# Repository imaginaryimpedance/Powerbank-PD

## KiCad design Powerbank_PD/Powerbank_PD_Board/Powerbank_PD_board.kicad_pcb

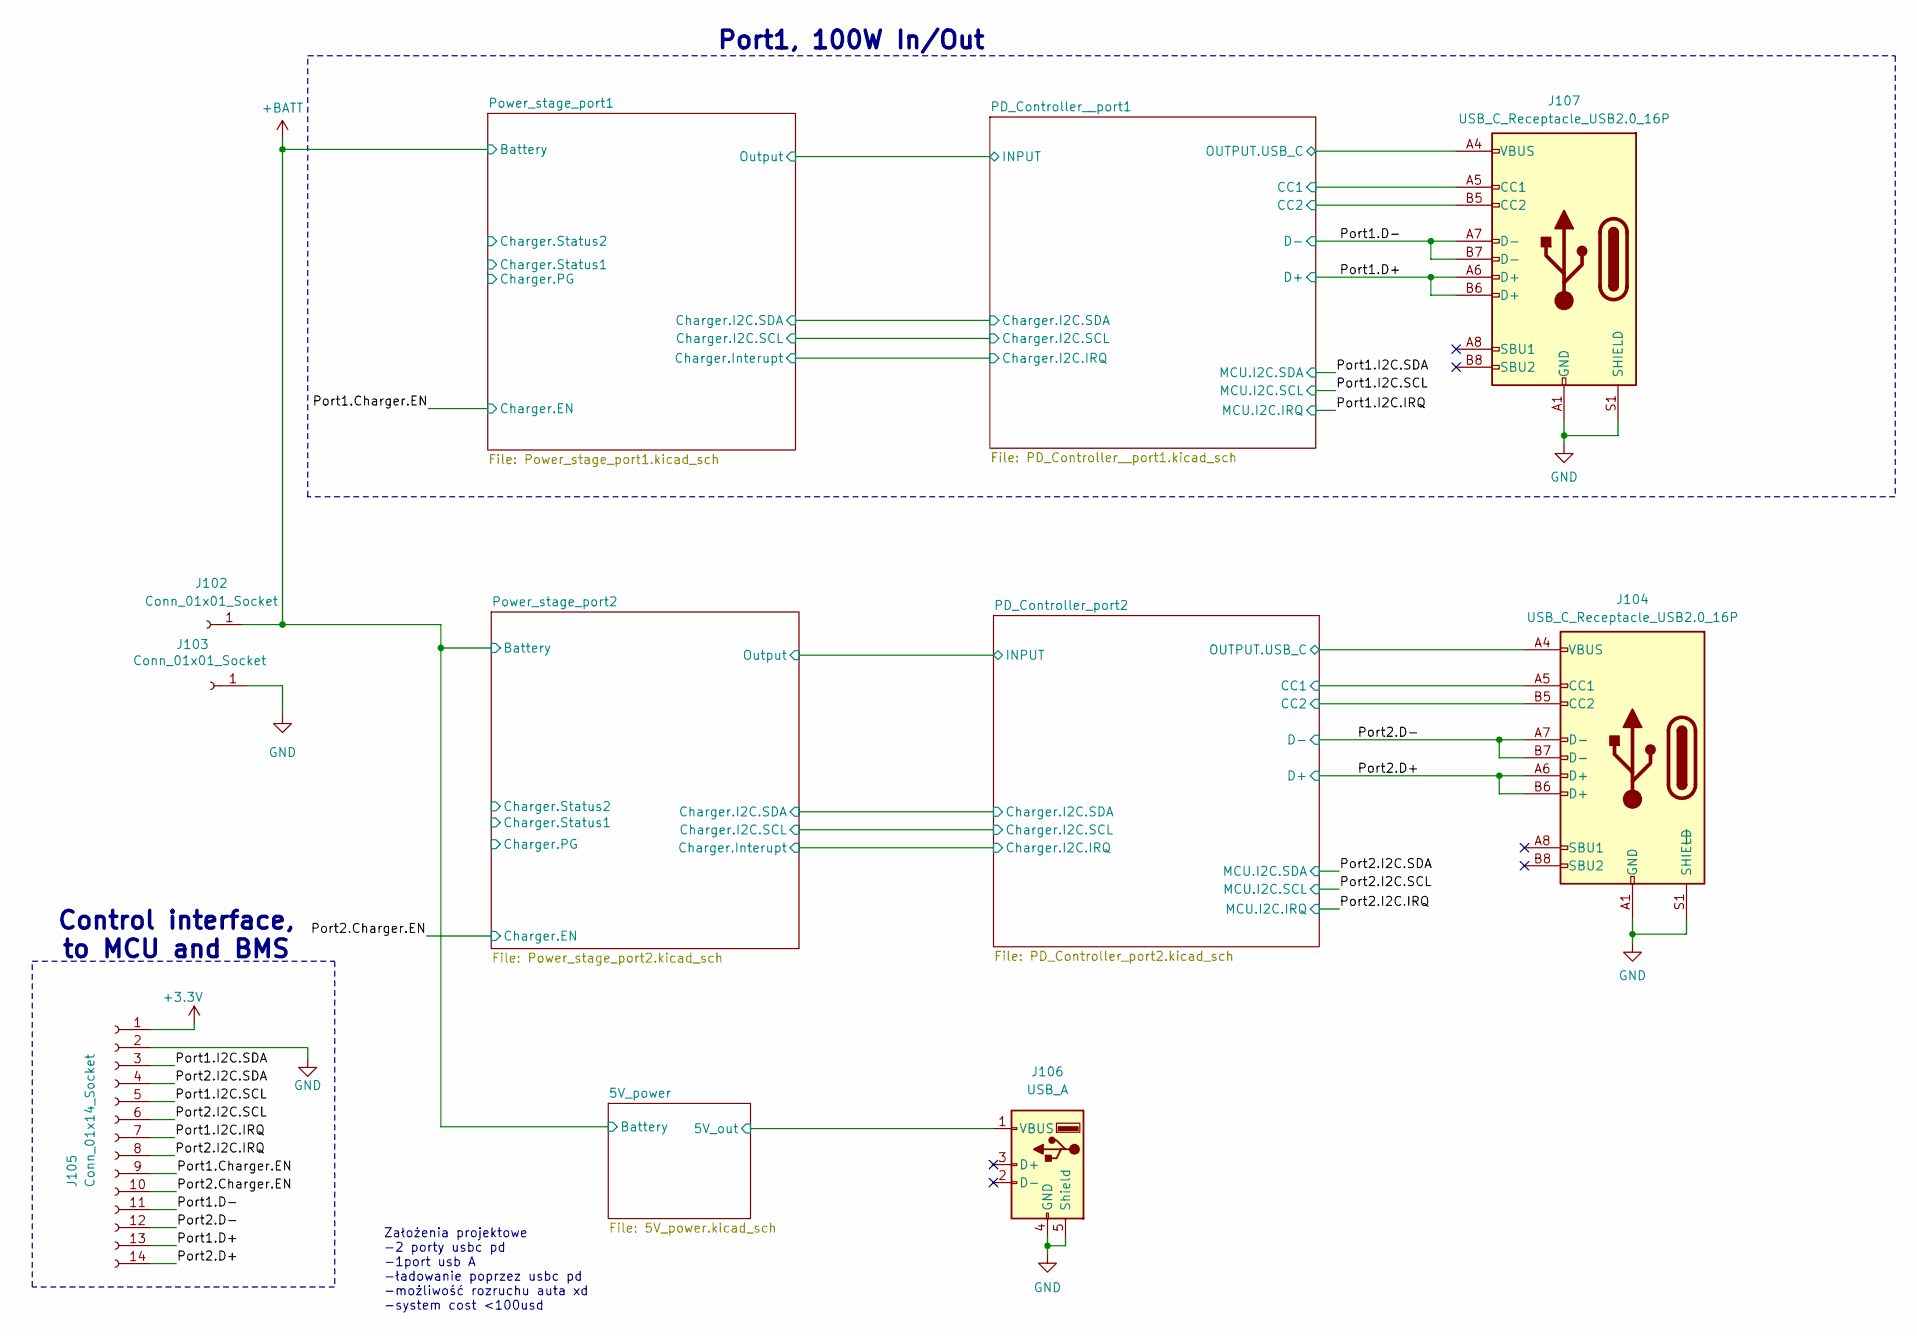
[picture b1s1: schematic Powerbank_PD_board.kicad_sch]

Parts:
J102, J103: Conn_01x01_Socket; TestPoint_Pad_4.0x4.0mm
J104, J107: USB_C_Receptacle_USB2.0_16P; USB_C_Receptacle_GCT_USB4110
J105: Conn_01x14_Socket; PinHeader_2x07_P1.00mm_Vertical_SMD
J106: USB_A; USB_A_CNCTech_1001-011-01101_Horizontal

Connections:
+3.3V: J105.1; also elsewhere on the board
+5V: J106.1 (VBUS); also elsewhere on the board
+BATT: J102.1; also elsewhere on the board
/PD_Controller__port1/CC1: J107.A5 (CC1); also elsewhere on the board
/PD_Controller__port1/CC2: J107.B5 (CC2); also elsewhere on the board
/PD_Controller__port1/OUTPUT.USB_C: J107.A4 (VBUS), J107.A9 (VBUS), J107.B4 (VBUS), J107.B9 (VBUS); also elsewhere on the board
/PD_Controller_port2/CC1: J104.A5 (CC1); also elsewhere on the board
/PD_Controller_port2/CC2: J104.B5 (CC2); also elsewhere on the board
/PD_Controller_port2/OUTPUT.USB_C: J104.A4 (VBUS), J104.A9 (VBUS), J104.B4 (VBUS), J104.B9 (VBUS); also elsewhere on the board
/Port1.Charger.EN: J105.9; also elsewhere on the board
/Port1.D+: J105.13, J107.A6 (D+), J107.B6 (D+); also elsewhere on the board
/Port1.D-: J105.11, J107.A7 (D-), J107.B7 (D-); also elsewhere on the board
/Port1.I2C.IRQ: J105.7; also elsewhere on the board
/Port1.I2C.SCL: J105.5; also elsewhere on the board
/Port1.I2C.SDA: J105.3; also elsewhere on the board
/Port2.Charger.EN: J105.10; also elsewhere on the board
/Port2.D+: J104.A6 (D+), J104.B6 (D+), J105.14; also elsewhere on the board
/Port2.D-: J104.A7 (D-), J104.B7 (D-), J105.12; also elsewhere on the board
/Port2.I2C.IRQ: J105.8; also elsewhere on the board
/Port2.I2C.SCL: J105.6; also elsewhere on the board
/Port2.I2C.SDA: J105.4; also elsewhere on the board
GND: J103.1, J104.A1 (GND), J104.A12 (GND), J104.B1 (GND), J104.B12 (GND), J104.S1 (SHIELD), J105.2, J106.4 (GND), J106.5 (Shield), J107.A1 (GND), J107.A12 (GND), J107.B1 (GND), J107.B12 (GND), J107.S1 (SHIELD); also elsewhere on the board

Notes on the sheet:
Control interface, to MCU and BMS
Założenia projektowe -2 porty usbc pd -1port usb A -ładowanie poprzez usbc pd -możliwość rozruchu auta xd -system cost <100usd
Port1, 100W In/Out

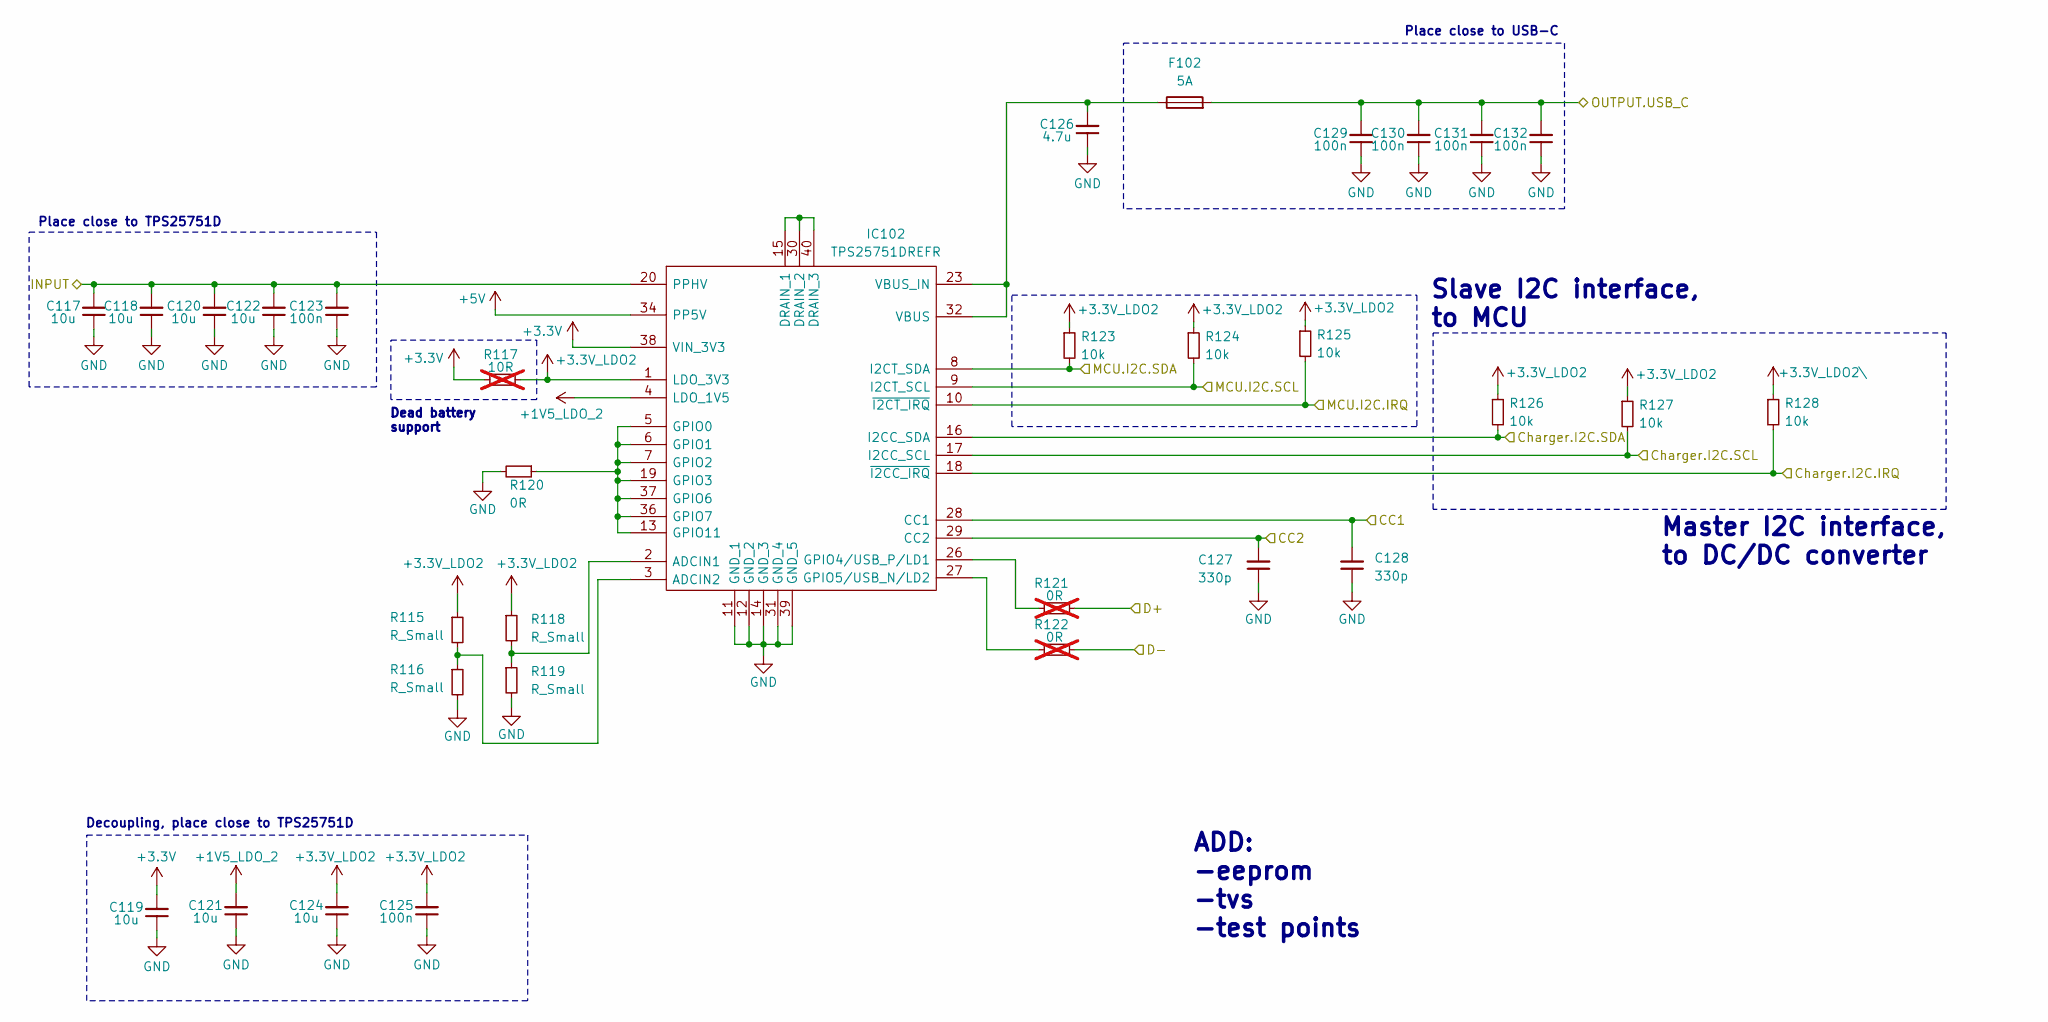
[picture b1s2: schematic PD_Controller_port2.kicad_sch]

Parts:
C117, C118, C119, C120, C121, C122, C124: 10u; C_0603_1608Metric
C123, C125, C129, C130, C131, C132: 100n; C_0603_1608Metric
C126: 4.7u; C_0603_1608Metric
C127, C128: 330p; C_0603_1608Metric
F102: 5A; Fuse_1206_3216Metric
IC102: TPS25751DREFR; Manufacturer_Part_Number TPS25751DREFR; Mouser Part Number 595-TPS25751DREFR
R115, R116, R118, R119: R_Small; R_0603_1608Metric
R117: 10R; R_0603_1608Metric; not fitted
R120: 0R; R_0603_1608Metric
R121, R122: 0R; R_0603_1608Metric; not fitted
R123, R124, R125, R126, R127, R128: 10k; R_0603_1608Metric

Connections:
+1V5_LDO_2: C121.2, IC102.4 (LDO_1V5)
+3.3V: C119.2, IC102.38 (VIN_3V3), R117.1; also elsewhere on the board
+3.3V_LDO2: C124.2, C125.2, IC102.1 (LDO_3V3), R115.1, R117.2, R118.1, R123.1, R124.1, R125.1, R126.1, R127.1
+3.3V_LDO2\: R128.1
+5V: IC102.34 (PP5V); also elsewhere on the board
/PD_Controller_port2/CC1: C128.2, IC102.28 (CC1); also elsewhere on the board
/PD_Controller_port2/CC2: C127.2, IC102.29 (CC2); also elsewhere on the board
/PD_Controller_port2/Charger.I2C.IRQ: IC102.18 (~I2CC_IRQ), R128.2; also elsewhere on the board
/PD_Controller_port2/Charger.I2C.SCL: IC102.17 (I2CC_SCL), R127.2; also elsewhere on the board
/PD_Controller_port2/Charger.I2C.SDA: IC102.16 (I2CC_SDA), R126.2; also elsewhere on the board
/PD_Controller_port2/INPUT: C117.2, C118.2, C120.2, C122.2, C123.2, IC102.20 (PPHV); also elsewhere on the board
/PD_Controller_port2/OUTPUT.USB_C: C129.2, C130.2, C131.2, C132.2, F102.2; also elsewhere on the board
/Port2.D+: R121.2; also elsewhere on the board
/Port2.D-: R122.2; also elsewhere on the board
/Port2.I2C.IRQ: IC102.10 (~I2CT_IRQ), R125.2; also elsewhere on the board
/Port2.I2C.SCL: IC102.9 (I2CT_SCL), R124.2; also elsewhere on the board
/Port2.I2C.SDA: IC102.8 (I2CT_SDA), R123.2; also elsewhere on the board
GND: C117.1, C118.1, C119.1, C120.1, C121.1, C122.1, C123.1, C124.1, C125.1, C126.1, C127.1, C128.1, C129.1, C130.1, C131.1, C132.1, IC102.11 (GND_1), IC102.12 (GND_2), IC102.14 (GND_3), IC102.31 (GND_4), IC102.39 (GND_5), R116.2, R119.2, R120.2; also elsewhere on the board
unnamed: IC102.2 (ADCIN1), R118.2, R119.1
unnamed: IC102.3 (ADCIN2), R115.2, R116.1
unnamed: IC102.15 (DRAIN_1), IC102.30 (DRAIN_2), IC102.40 (DRAIN_3)
unnamed: IC102.5 (GPIO0), IC102.6 (GPIO1), IC102.7 (GPIO2), IC102.13 (GPIO11), IC102.19 (GPIO3), IC102.36 (GPIO7), IC102.37 (GPIO6), R120.1
unnamed: IC102.26 (GPIO4/USB_P/LD1), R121.1
unnamed: IC102.27 (GPIO5/USB_N/LD2), R122.1
unnamed: C126.2, F102.1, IC102.23 (VBUS_IN), IC102.32 (VBUS)

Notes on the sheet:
Slave I2C interface, to MCU
Master I2C interface, to DC/DC converter
ADD: -eeprom -tvs -test points
Place close to USB-C
Dead battery support
Decoupling, place close to TPS25751D
Place close to TPS25751D

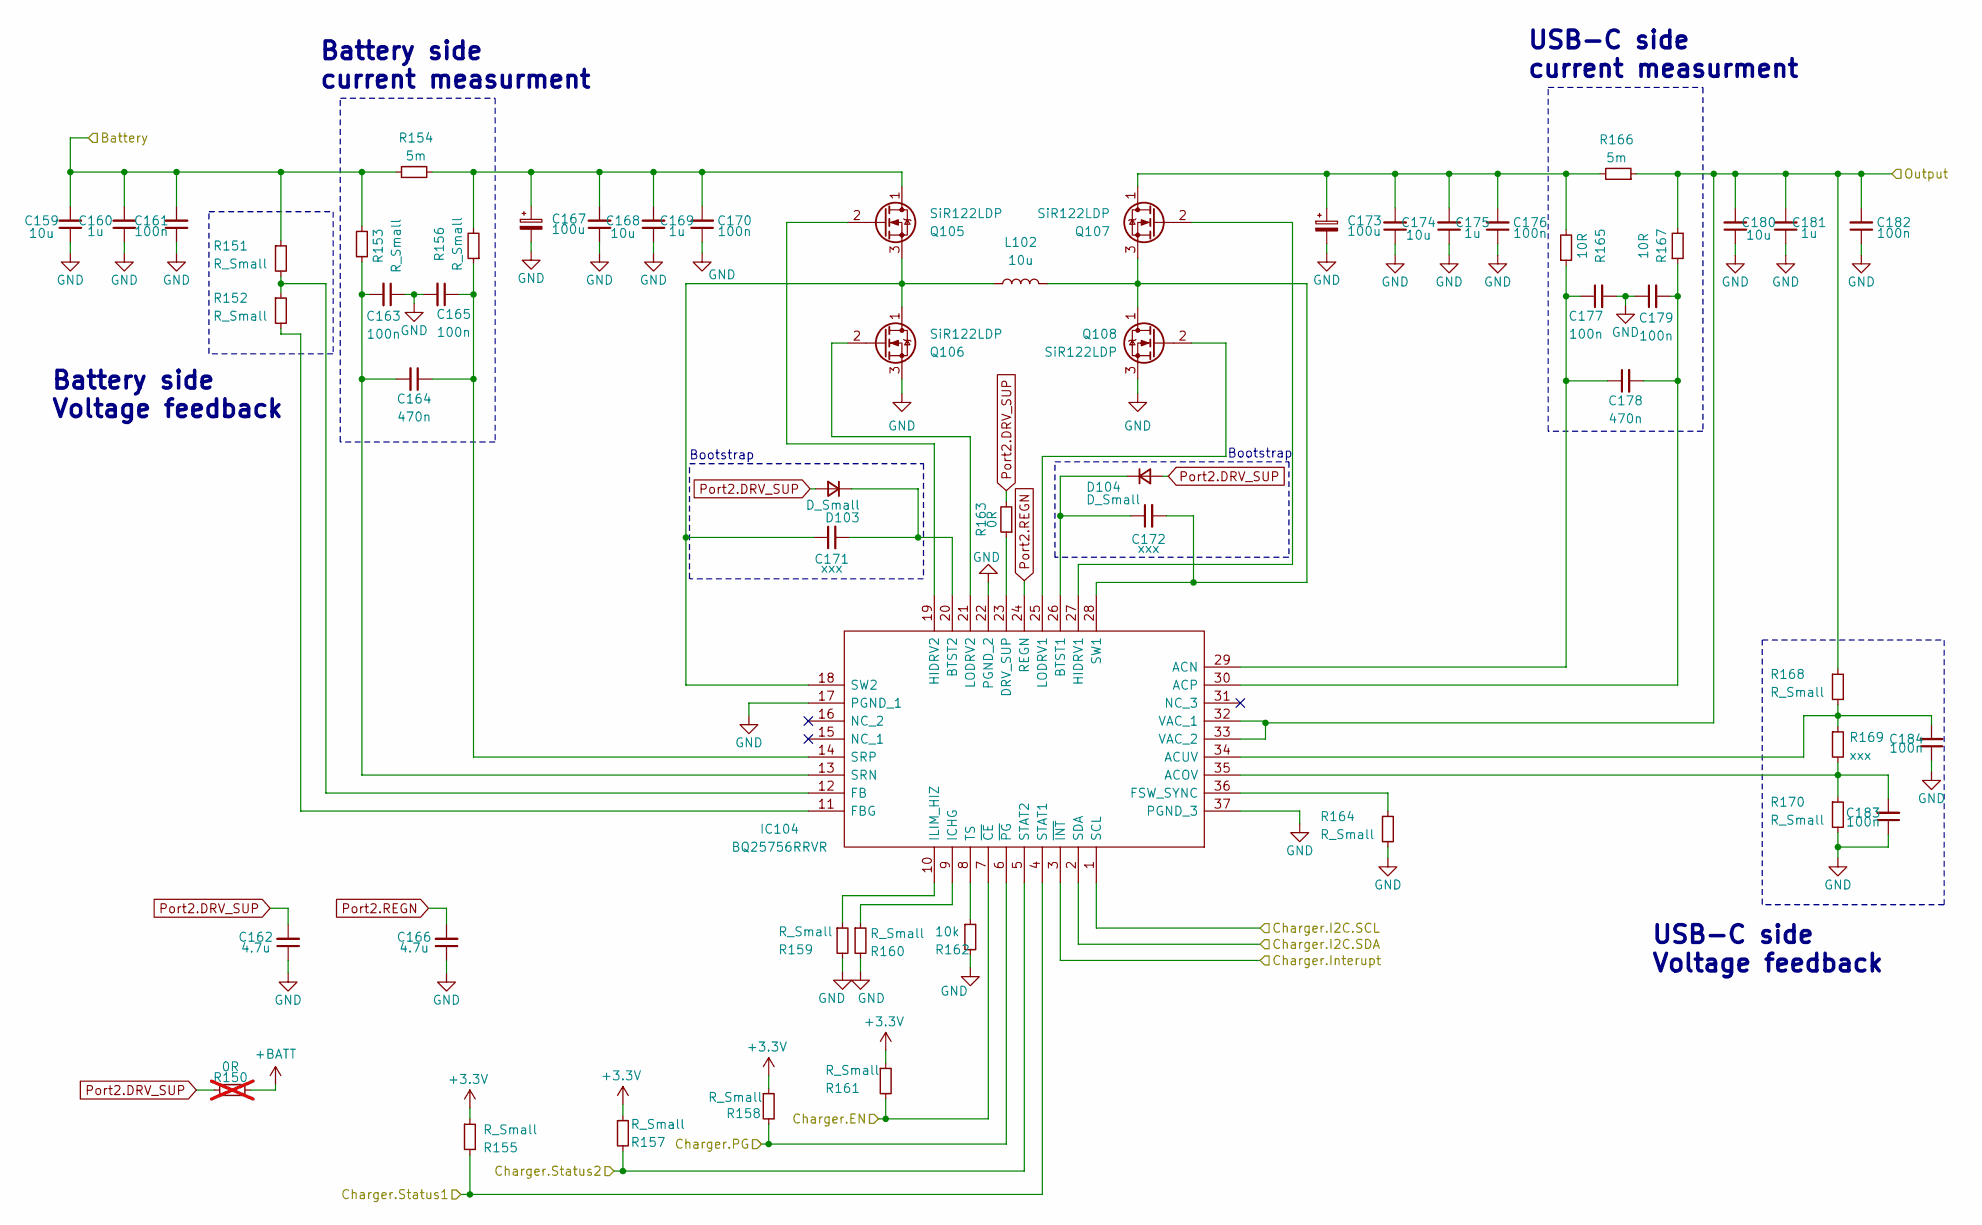
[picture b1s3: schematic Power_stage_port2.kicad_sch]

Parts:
C159, C168, C174: 10u; C_0603_1608Metric
C160, C169, C175: 1u; C_0603_1608Metric
C161, C163, C165, C170, C176, C177, C179, C183, C184: 100n; C_0603_1608Metric
C162, C166: 4.7u; C_0603_1608Metric
C164, C178: 470n; C_0603_1608Metric
C167, C173: 100u; CP_Elec_6.3x7.7
C171, C172: xxx; C_0603_1608Metric
C180: 10u; C_0805_2012Metric
C181: 1u; C_0805_2012Metric
C182: 100n; C_0805_2012Metric
D103, D104: D_Small; D_SOD-123
IC104: BQ25756RRVR; QFN50P500X600X100-37N-D; Manufacturer_Part_Number BQ25756RRVR; Mouser Part Number 595-BQ25756RRVR
L102: 10u; L_Coilcraft_XxL4040
Q105, Q106, Q107, Q108: SiR122LDP; PowerPAK_SO-8_Single
R150: 0R; R_0603_1608Metric; not fitted
R151, R152, R153, R155, R156, R157, R158, R159, R160, R161, R164, R168, R170: R_Small; R_0603_1608Metric
R154, R166: 5m; R_2512_6332Metric
R162: 10k; R_0603_1608Metric
R163: 0R; R_0603_1608Metric
R165, R167: 10R; R_0603_1608Metric
R169: xxx; R_0603_1608Metric

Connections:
+3.3V: R155.1, R157.1, R158.1, R161.1; also elsewhere on the board
+BATT: C159.2, C160.2, C161.2, R150.1, R151.1, R153.2, R154.1; also elsewhere on the board
/PD_Controller_port2/Charger.I2C.IRQ: IC104.3 (~INT); also elsewhere on the board
/PD_Controller_port2/Charger.I2C.SCL: IC104.1 (SCL); also elsewhere on the board
/PD_Controller_port2/Charger.I2C.SDA: IC104.2 (SDA); also elsewhere on the board
/PD_Controller_port2/INPUT: C180.2, C181.2, C182.2, IC104.32 (VAC_1), IC104.33 (VAC_2), R166.1, R167.2, R168.1; also elsewhere on the board
/Port2.Charger.EN: IC104.7 (~CE), R161.2; also elsewhere on the board
/Power_stage_port2/Charger.PG: IC104.6 (~PG), R158.2
/Power_stage_port2/Charger.Status1: IC104.4 (STAT1), R155.2
/Power_stage_port2/Charger.Status2: IC104.5 (STAT2), R157.2
GND: C159.1, C160.1, C161.1, C162.1, C163.1, C165.2, C166.1, C167.2, C168.1, C169.1, C170.1, C173.2, C174.1, C175.1, C176.1, C177.2, C179.1, C180.1, C181.1, C182.1, C183.1, C184.1, IC104.17 (PGND_1), IC104.22 (PGND_2), IC104.37 (PGND_3), Q106.3 (S), Q108.3 (S), R159.2, R160.2, R162.2, R164.2, R170.2; also elsewhere on the board
unnamed: C171.2, D103.1 (K), IC104.20 (BTST2)
unnamed: C172.1, D104.1 (K), IC104.26 (BTST1)
unnamed: C177.1, C178.1, IC104.29 (ACN), R165.1
unnamed: C183.2, IC104.35 (ACOV), R169.2, R170.1
unnamed: C178.2, C179.2, IC104.30 (ACP), R167.1
unnamed: C184.2, IC104.34 (ACUV), R168.2, R169.1
unnamed: IC104.23 (DRV_SUP), R163.1
unnamed: IC104.12 (FB), R151.2, R152.1
unnamed: IC104.11 (FBG), R152.2
unnamed: IC104.36 (FSW_SYNC), R164.1
unnamed: IC104.27 (HIDRV1), Q107.2 (G)
unnamed: IC104.19 (HIDRV2), Q105.2 (G)
unnamed: IC104.9 (ICHG), R160.1
unnamed: IC104.10 (ILIM_HIZ), R159.1
unnamed: IC104.25 (LODRV1), Q108.2 (G)
unnamed: IC104.21 (LODRV2), Q106.2 (G)
unnamed: C163.2, C164.2, IC104.13 (SRN), R153.1
unnamed: C164.1, C165.1, IC104.14 (SRP), R156.1
unnamed: C172.2, IC104.28 (SW1), L102.2, Q107.3 (S), Q108.1 (D)
unnamed: C171.1, IC104.18 (SW2), L102.1, Q105.3 (S), Q106.1 (D)
unnamed: IC104.8 (TS), R162.1
unnamed: C167.1, C168.2, C169.2, C170.2, Q105.1 (D), R154.2, R156.2
unnamed: C173.1, C174.2, C175.2, C176.2, Q107.1 (D), R165.2, R166.2
Port2.DRV_SUP: C162.2, D103.2 (A), D104.2 (A), R150.2, R163.2
Port2.REGN: C166.2, IC104.24 (REGN)

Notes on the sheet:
Bootstrap
USB-C side current measurment
Battery side current measurment
Battery side Voltage feedback
USB-C side Voltage feedback

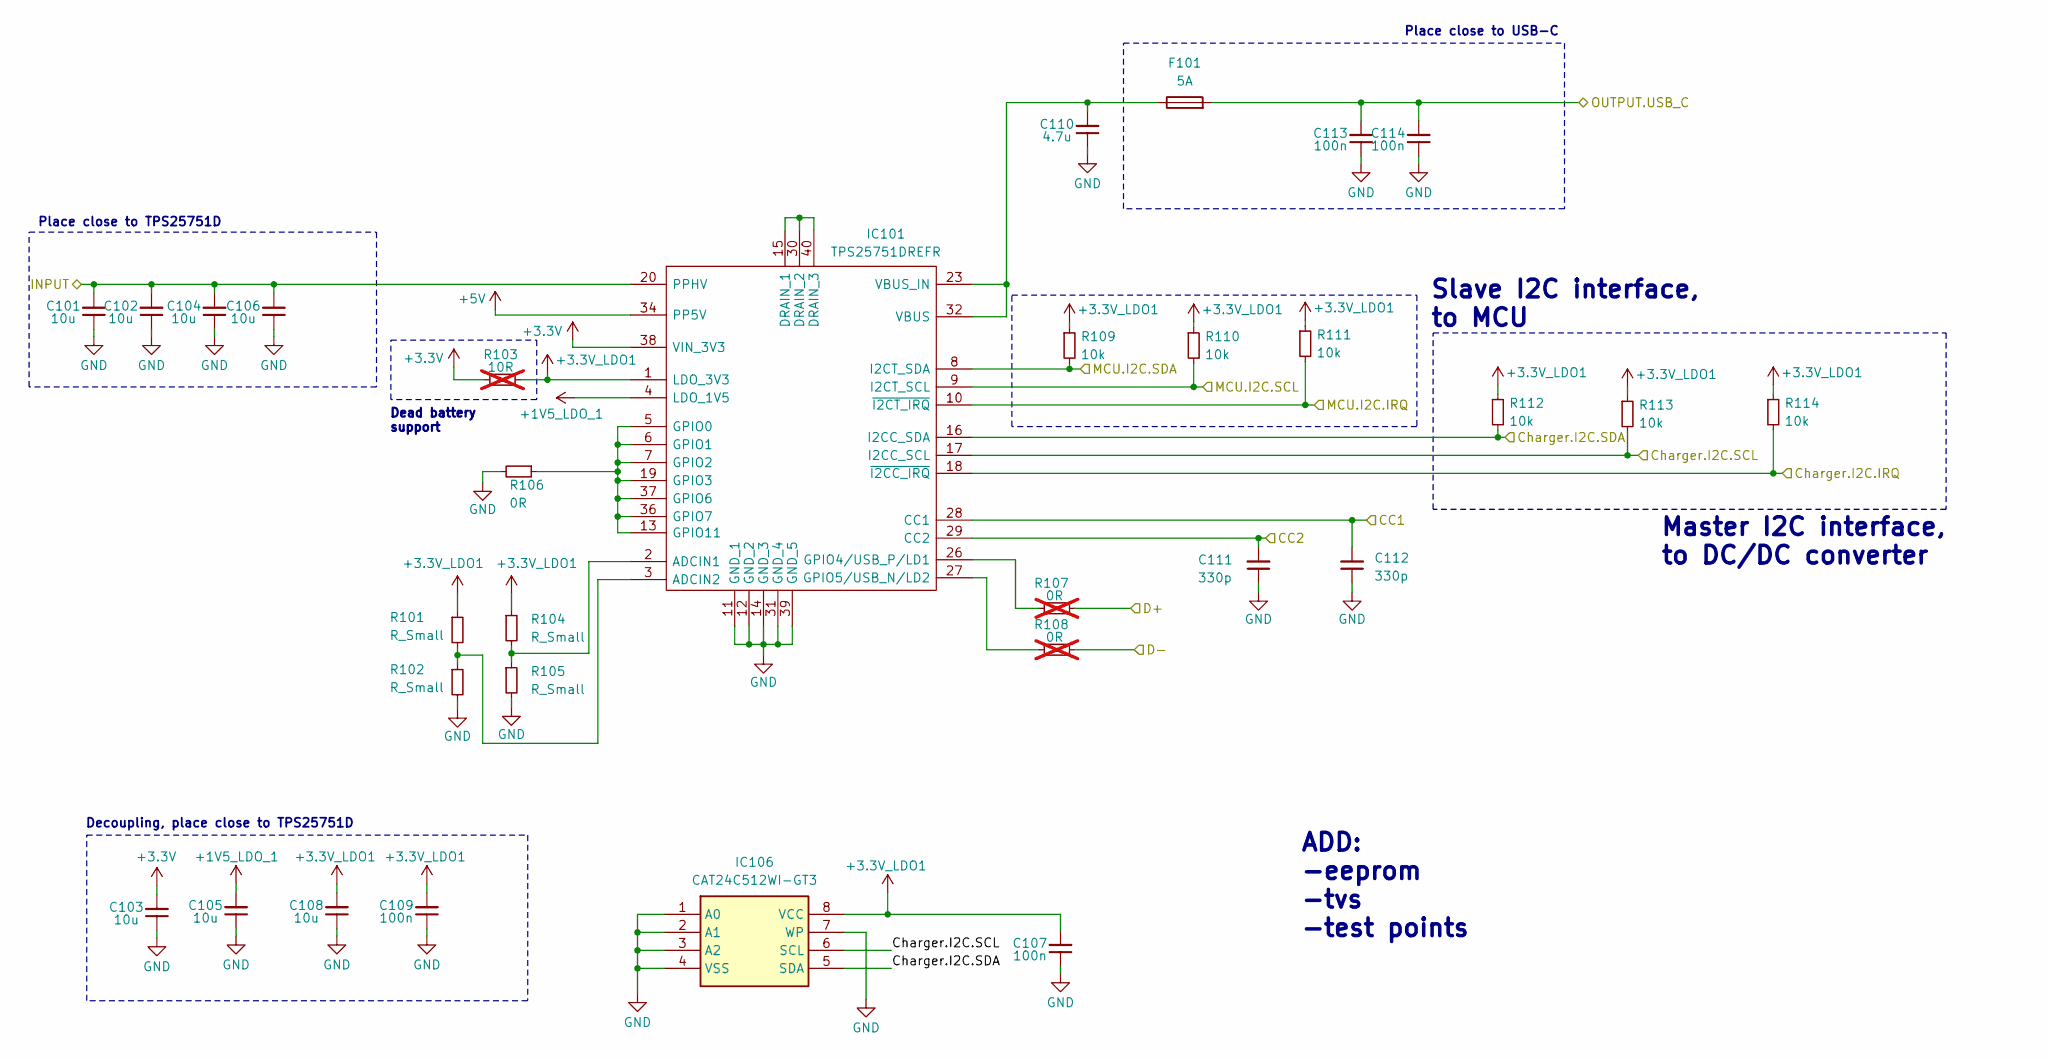
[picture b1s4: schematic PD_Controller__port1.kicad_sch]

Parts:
C101, C102, C104, C106: 10u; C_1206_3216Metric
C103, C105, C108: 10u; C_0603_1608Metric
C107, C109: 100n; C_0603_1608Metric
C110: 4.7u; C_0603_1608Metric
C111, C112: 330p; C_0603_1608Metric
C113, C114: 100n; C_1206_3216Metric
F101: 5A; Fuse_1206_3216Metric
IC101: TPS25751DREFR; Manufacturer_Part_Number TPS25751DREFR; Mouser Part Number 595-TPS25751DREFR
IC106: CAT24C512WI-GT3; SOIC127P600X175-8N; Manufacturer_Part_Number CAT24C512WI-GT3; Mouser Part Number 863-CAT24C512WI-GT3
R101, R102, R104, R105: R_Small; R_0603_1608Metric
R103: 10R; R_0603_1608Metric; not fitted
R106: 0R; R_0603_1608Metric
R107, R108: 0R; R_0603_1608Metric; not fitted
R109, R110, R111, R112, R113, R114: 10k; R_0603_1608Metric

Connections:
+1V5_LDO_1: C105.2, IC101.4 (LDO_1V5)
+3.3V: C103.2, IC101.38 (VIN_3V3), R103.1; also elsewhere on the board
+3.3V_LDO1: C107.2, C108.2, C109.2, IC101.1 (LDO_3V3), IC106.8 (VCC), R101.1, R103.2, R104.1, R109.1, R110.1, R111.1, R112.1, R113.1, R114.1
+5V: IC101.34 (PP5V); also elsewhere on the board
/PD_Controller__port1/CC1: C112.2, IC101.28 (CC1); also elsewhere on the board
/PD_Controller__port1/CC2: C111.2, IC101.29 (CC2); also elsewhere on the board
/PD_Controller__port1/Charger.I2C.IRQ: IC101.18 (~I2CC_IRQ), R114.2; also elsewhere on the board
/PD_Controller__port1/Charger.I2C.SCL: IC101.17 (I2CC_SCL), IC106.6 (SCL), R113.2; also elsewhere on the board
/PD_Controller__port1/Charger.I2C.SDA: IC101.16 (I2CC_SDA), IC106.5 (SDA), R112.2; also elsewhere on the board
/PD_Controller__port1/INPUT: C101.2, C102.2, C104.2, C106.2, IC101.20 (PPHV); also elsewhere on the board
/PD_Controller__port1/OUTPUT.USB_C: C113.2, C114.2, F101.2; also elsewhere on the board
/Port1.D+: R107.2; also elsewhere on the board
/Port1.D-: R108.2; also elsewhere on the board
/Port1.I2C.IRQ: IC101.10 (~I2CT_IRQ), R111.2; also elsewhere on the board
/Port1.I2C.SCL: IC101.9 (I2CT_SCL), R110.2; also elsewhere on the board
/Port1.I2C.SDA: IC101.8 (I2CT_SDA), R109.2; also elsewhere on the board
GND: C101.1, C102.1, C103.1, C104.1, C105.1, C106.1, C107.1, C108.1, C109.1, C110.1, C111.1, C112.1, C113.1, C114.1, IC101.11 (GND_1), IC101.12 (GND_2), IC101.14 (GND_3), IC101.31 (GND_4), IC101.39 (GND_5), IC106.1 (A0), IC106.2 (A1), IC106.3 (A2), IC106.4 (VSS), IC106.7 (WP), R102.2, R105.2, R106.2; also elsewhere on the board
unnamed: IC101.2 (ADCIN1), R104.2, R105.1
unnamed: IC101.3 (ADCIN2), R101.2, R102.1
unnamed: IC101.15 (DRAIN_1), IC101.30 (DRAIN_2), IC101.40 (DRAIN_3)
unnamed: IC101.5 (GPIO0), IC101.6 (GPIO1), IC101.7 (GPIO2), IC101.13 (GPIO11), IC101.19 (GPIO3), IC101.36 (GPIO7), IC101.37 (GPIO6), R106.1
unnamed: IC101.26 (GPIO4/USB_P/LD1), R107.1
unnamed: IC101.27 (GPIO5/USB_N/LD2), R108.1
unnamed: C110.2, F101.1, IC101.23 (VBUS_IN), IC101.32 (VBUS)

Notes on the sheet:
Slave I2C interface, to MCU
Master I2C interface, to DC/DC converter
ADD: -eeprom -tvs -test points
Place close to USB-C
Dead battery support
Decoupling, place close to TPS25751D
Place close to TPS25751D

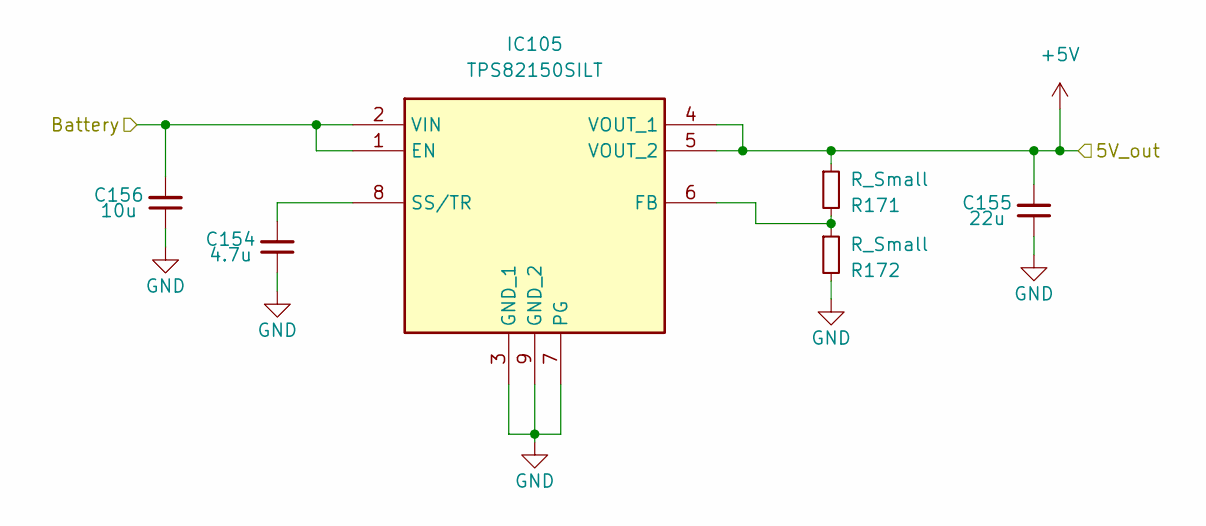
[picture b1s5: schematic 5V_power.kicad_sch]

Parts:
C154: 4.7u; C_0603_1608Metric
C155: 22u; C_1206_3216Metric
C156: 10u; C_1206_3216Metric
IC105: TPS82150SILT; SIL0008D; Manufacturer_Part_Number TPS82150SILT; Mouser Part Number 595-TPS82150SILT
R171, R172: R_Small; R_0603_1608Metric

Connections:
+5V: C155.2, IC105.4 (VOUT_1), IC105.5 (VOUT_2), R171.1; also elsewhere on the board
+BATT: C156.2, IC105.1 (EN), IC105.2 (VIN); also elsewhere on the board
GND: C154.1, C155.1, C156.1, IC105.3 (GND_1), IC105.7 (PG), IC105.9 (GND_2), R172.2; also elsewhere on the board
unnamed: IC105.6 (FB), R171.2, R172.1
unnamed: C154.2, IC105.8 (SS/TR)

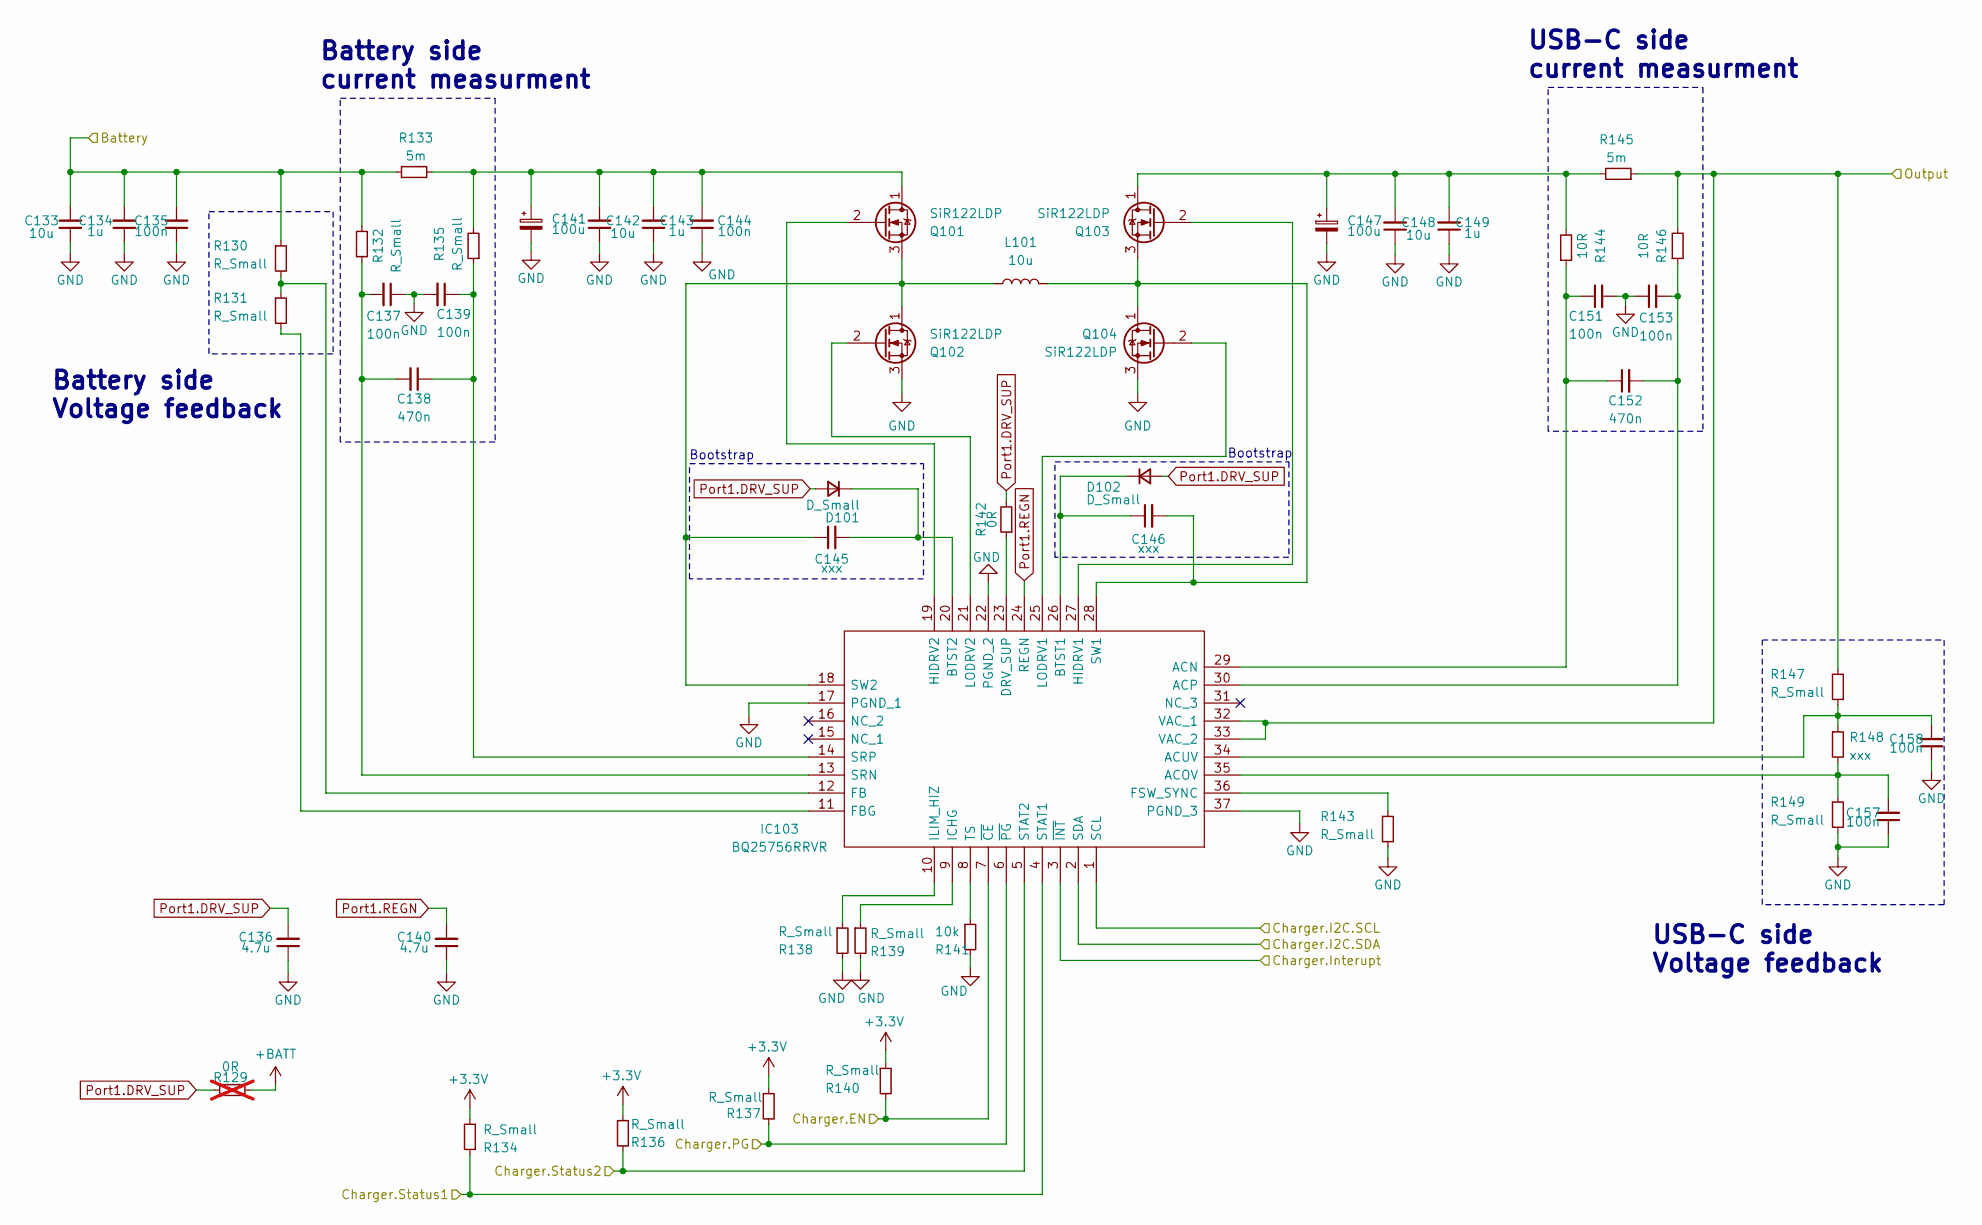
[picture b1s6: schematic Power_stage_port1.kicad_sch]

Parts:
C133, C142, C148: 10u; C_1206_3216Metric
C134, C143, C149: 1u; C_1206_3216Metric
C135, C144: 100n; C_1206_3216Metric
C136, C140: 4.7u; C_0603_1608Metric
C137, C139, C151, C153, C157, C158: 100n; C_0603_1608Metric
C138, C152: 470n; C_0603_1608Metric
C141, C147: 100u; CP_Elec_6.3x7.7
C145, C146: xxx; C_0603_1608Metric
D101, D102: D_Small; D_SOD-123
IC103: BQ25756RRVR; QFN50P500X600X100-37N-D; Manufacturer_Part_Number BQ25756RRVR; Mouser Part Number 595-BQ25756RRVR
L101: 10u; XAL1010
Q101, Q102, Q103, Q104: SiR122LDP; PowerPAK_SO-8_Single
R129: 0R; R_0603_1608Metric; not fitted
R130, R131, R132, R134, R135, R136, R137, R138, R139, R140, R143, R147, R149: R_Small; R_0603_1608Metric
R133, R145: 5m; R_2512_6332Metric
R141: 10k; R_0603_1608Metric
R142: 0R; R_0603_1608Metric
R144, R146: 10R; R_0603_1608Metric
R148: xxx; R_0603_1608Metric

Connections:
+3.3V: R134.1, R136.1, R137.1, R140.1; also elsewhere on the board
+BATT: C133.2, C134.2, C135.2, R129.1, R130.1, R132.2, R133.1; also elsewhere on the board
/PD_Controller__port1/Charger.I2C.IRQ: IC103.3 (~INT); also elsewhere on the board
/PD_Controller__port1/Charger.I2C.SCL: IC103.1 (SCL); also elsewhere on the board
/PD_Controller__port1/Charger.I2C.SDA: IC103.2 (SDA); also elsewhere on the board
/PD_Controller__port1/INPUT: IC103.32 (VAC_1), IC103.33 (VAC_2), R145.1, R146.2, R147.1; also elsewhere on the board
/Port1.Charger.EN: IC103.7 (~CE), R140.2; also elsewhere on the board
/Power_stage_port1/Charger.PG: IC103.6 (~PG), R137.2
/Power_stage_port1/Charger.Status1: IC103.4 (STAT1), R134.2
/Power_stage_port1/Charger.Status2: IC103.5 (STAT2), R136.2
GND: C133.1, C134.1, C135.1, C136.1, C137.1, C139.2, C140.1, C141.2, C142.1, C143.1, C144.1, C147.2, C148.1, C149.1, C151.2, C153.1, C157.1, C158.1, IC103.17 (PGND_1), IC103.22 (PGND_2), IC103.37 (PGND_3), Q102.3 (S), Q104.3 (S), R138.2, R139.2, R141.2, R143.2, R149.2; also elsewhere on the board
unnamed: C145.2, D101.1 (K), IC103.20 (BTST2)
unnamed: C146.1, D102.1 (K), IC103.26 (BTST1)
unnamed: C151.1, C152.1, IC103.29 (ACN), R144.1
unnamed: C157.2, IC103.35 (ACOV), R148.2, R149.1
unnamed: C152.2, C153.2, IC103.30 (ACP), R146.1
unnamed: C158.2, IC103.34 (ACUV), R147.2, R148.1
unnamed: IC103.23 (DRV_SUP), R142.1
unnamed: IC103.12 (FB), R130.2, R131.1
unnamed: IC103.11 (FBG), R131.2
unnamed: IC103.36 (FSW_SYNC), R143.1
unnamed: IC103.27 (HIDRV1), Q103.2 (G)
unnamed: IC103.19 (HIDRV2), Q101.2 (G)
unnamed: IC103.9 (ICHG), R139.1
unnamed: IC103.10 (ILIM_HIZ), R138.1
unnamed: IC103.25 (LODRV1), Q104.2 (G)
unnamed: IC103.21 (LODRV2), Q102.2 (G)
unnamed: C137.2, C138.2, IC103.13 (SRN), R132.1
unnamed: C138.1, C139.1, IC103.14 (SRP), R135.1
unnamed: C146.2, IC103.28 (SW1), L101.2, Q103.3 (S), Q104.1 (D)
unnamed: C145.1, IC103.18 (SW2), L101.1, Q101.3 (S), Q102.1 (D)
unnamed: IC103.8 (TS), R141.1
unnamed 99: C141.1, C142.2, C143.2, C144.2, Q101.1 (D), R133.2, R135.2; also elsewhere on the board
unnamed 100: C147.1, C148.2, C149.2, Q103.1 (D), R144.2, R145.2; also elsewhere on the board
Port1.DRV_SUP: C136.2, D101.2 (A), D102.2 (A), R129.2, R142.2
Port1.REGN: C140.2, IC103.24 (REGN)

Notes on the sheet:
Bootstrap
USB-C side current measurment
Battery side current measurment
Battery side Voltage feedback
USB-C side Voltage feedback
